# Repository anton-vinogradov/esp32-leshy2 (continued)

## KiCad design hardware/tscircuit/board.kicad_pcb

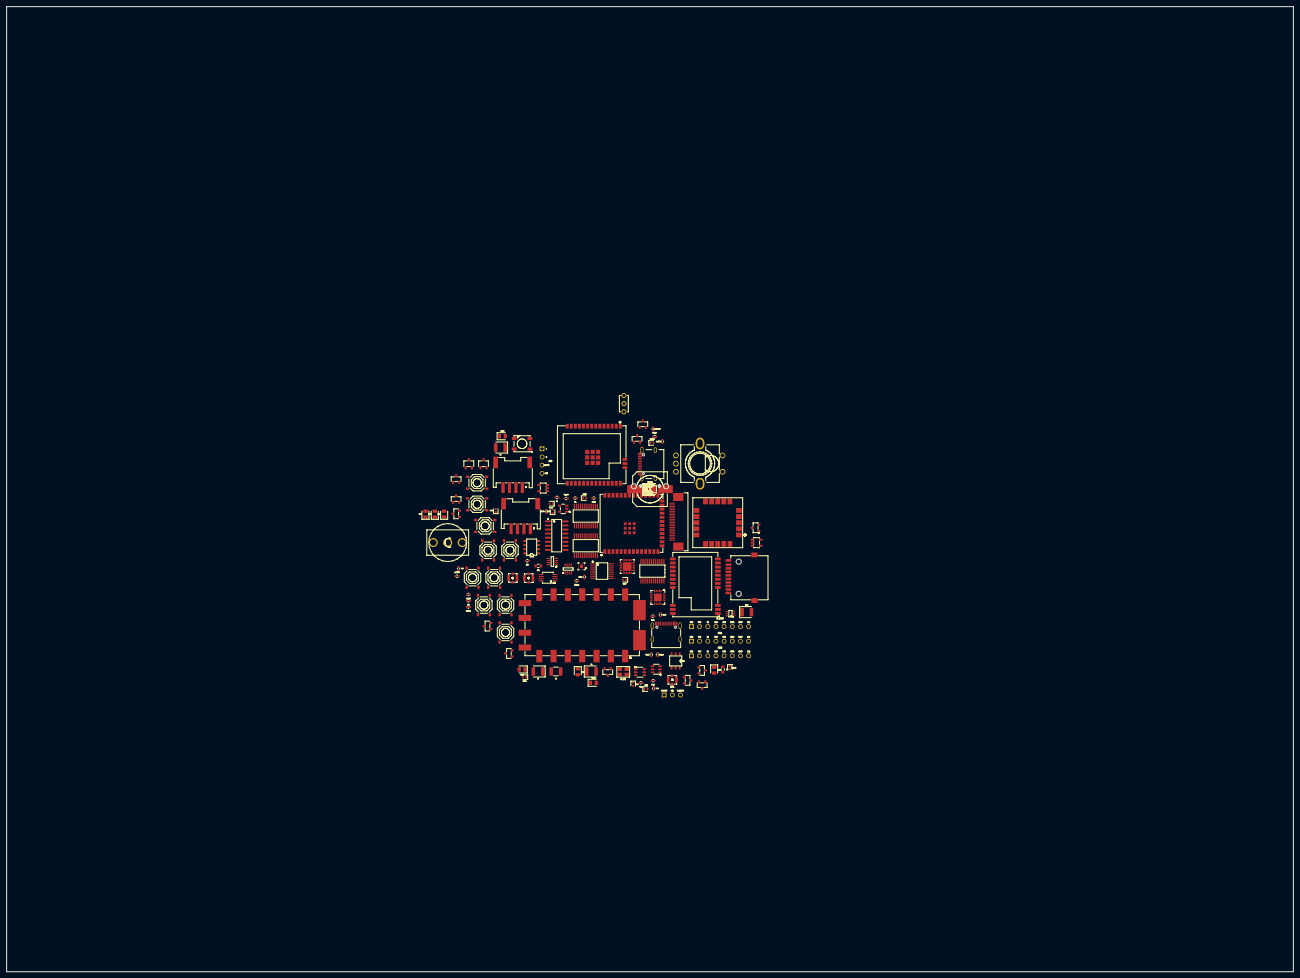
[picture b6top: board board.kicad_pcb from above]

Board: 2 copper layers, 400.0 x 300.0 mm, 191 parts (0 on the bottom side), 177 nets, no tracks yet.

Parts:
BL1: chip_soic6
BT1: chip_pinrow3
BT40: chip
CL1, CL2: 12pF; capacitor_cap0402
C_C5EN: 1uF; capacitor_cap0402
Cb20, Cb21, Cb22: 150uF; capacitor_cap1210
Cb23, Cb25: 100uF; capacitor_cap1210
Cbat: 10uF; capacitor_cap0805
Cbst4, Cbst5: 100nF; capacitor_cap0402
Cbtst: 47nF; capacitor_cap0402
Cbulk31: 330uF; capacitor_cap1210
Cbulk40: 10uF; capacitor_cap0805
Cbyp31: 100nF; capacitor_cap0402
Ccpl_si: 100pF; capacitor_cap0402
Cd20, Cd21, Cd22, Cd23, Cd25: 100nF; capacitor_cap0402
Cdc: 100nF; capacitor_cap0402
Cds1: 100nF; capacitor_cap0402
Cen: 1uF; capacitor_cap0402
Cin3, Cin5: 22uF; capacitor_cap0805
Cin3a: 1uF; capacitor_cap0402
Cinn: 0.1uF; capacitor_cap0402
Cinp: 0.1uF; capacitor_cap0402
Cio40: 100nF; capacitor_cap0402
Cir: 100nF; capacitor_cap0402
Cjk1, Cjk2: 220uF; capacitor_cap1210
Cmic: 1uF; capacitor_cap0402
Cout3, Cout5: 22uF; capacitor_cap0805
Cout3a: 2.2uF; capacitor_cap0402
Cpmid: 10uF; capacitor_cap0805
Cregn: 4.7uF; capacitor_cap0805
Csd1: 10uF; capacitor_cap0805
Csd2: 100nF; capacitor_cap0402
Csns: 47uF; capacitor_cap1210
Cu14, Cu51: 100nF; capacitor_cap0402
Cvbus: 10uF; capacitor_cap0805
Cvbusic: 1uF; capacitor_cap0402
Cvc: 0.1uF; capacitor_cap0402
Cvcc4, Cvcc5: 0.1uF; capacitor_cap0402
Cvcc32: 10uF; capacitor_cap0805
Cvcc40: 100nF; capacitor_cap0402
Cvdd: 0.1uF; capacitor_cap0402
Cvdd30: 1uF; capacitor_cap0402
Cvdd30b: 100nF; capacitor_cap0402
Cx1, Cx2: 10pF; capacitor_cap0402
D1: 1MΩ; resistor_res0603
D40, D41, D42: chip
D50, D51, D52, D53, D54, D55, D56, D57: LED; led_0603
DS1: chip
F1: 50mΩ; resistor_res1210
J1, J2, J40, J41, J50: chip
J30: chip_pinrow4
J_ANT_CC: chip
J_ANT_SI: chip
J_ANT_UHF: chip
J_LCD: chip
L1, L3: 2.2µH; inductor_1210
L2: 4.7µH; inductor_1210
LS1: 4Ω; resistor_res1210
LS2: 10mΩ; resistor_res1210
Lm315, Lm433, Lm868, Lm915: 1nH; inductor_0402
MK1: 2.2kΩ; resistor_res0603
Q1, Q2, Q50, Q51, Q52, Q53, Q54, Q55, Q56, Q57, Q58: chip
R1: 52.3kΩ; resistor_res0402
R2, R4: 10kΩ; resistor_res0402
R3: 31.6kΩ; resistor_res0402
R40, R41: 4.7kΩ; resistor_res0402
RT1: 10kΩ; resistor_res0603
RT2: 30.1kΩ; resistor_res0402
R_C5BOOT, R_C5EN, R_C5S27: 10kΩ; resistor_res0402
R_EN3H: 100kΩ; resistor_res0402
R_EN3L: 47kΩ; resistor_res0402
R_HC138EN: 10kΩ; resistor_res0402
R_RE3A, R_RE5: 100kΩ; resistor_res0402
Raam4, Raam5: 100kΩ; resistor_res0402
Rbst4, Rbst5: 20Ω; resistor_res0402
Rcbset: 10Ω; resistor_res0402
Rcc1, Rcc2: 5.1kΩ; resistor_res0402
Rd50, Rd51, Rd52, Rd53, Rd54, Rd55, Rd56: 4.7kΩ; resistor_res0402
Ren: 10kΩ; resistor_res0402
Rilim: 383Ω; resistor_res0402
Rin32: 10kΩ; resistor_res0402
Rir: 47Ω; resistor_res0603
Rmid: 300Ω; resistor_res0402
RsumL: 10kΩ; resistor_res0402
RsumR: 10kΩ; resistor_res0402
Rts_top: 5.23kΩ; resistor_res0402
Rvc: 470Ω; resistor_res0402
Rvdd: 470Ω; resistor_res0402
Rvm: 2kΩ; resistor_res0402
SW1, SW10: chip
SW11, SW12, SW13: 10mΩ; resistor_res1210
SW_BACK: chip
SW_DN: chip
SW_F1, SW_F2: chip
SW_LF: chip
SW_OK: chip
SW_OPT: chip
SW_RT: chip
SW_STOP: chip
SW_UP: chip
U2, U3, U4, U5, U6, U10, U11, U12, U13, U14, U23, U24, U25, U27, U28, U30, U31, U32, U33, U40, U50, U51: chip
U21, U22: chip_pinrow8_p2.54_doublerow
U44: chip_soic8
a_Rbias: 4.7kΩ; resistor_res0402
a_Y1: chip
m_U20: chip
rf_Rbias: 56kΩ; resistor_res0402
rf_U20: chip_pinrow8_p2.54_doublerow
rf_Y1: rf_Y1; crystal_crystal_3215_2

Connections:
.BT1 > .P_PLUS to .F1 > .pin1: BT1.1, F1.1
.Cbst4 > .pin1 to .U4 > .BST: Cbst4.1, U4.5
.Cbst4 > .pin2 to .Rbst4 > .pin1: Cbst4.2, Rbst4.1
.Cbst5 > .pin1 to .U5 > .BST: Cbst5.1, U5.5
.Cbst5 > .pin2 to .Rbst5 > .pin1: Cbst5.2, Rbst5.1
.Cbtst > .pin1 to .U2 > .BTST: Cbtst.1, U2.12
.Cinp > .pin2 to .U32 > .IN_POS: Cinp.2, U32.3
.Cjk1 > .pin2 to .J30 > .L: Cjk1.2, J30.1
.Cjk2 > .pin2 to .J30 > .R: Cjk2.2, J30.2
.Cmic > .pin2 to .U31 > .MIC_IN: Cmic.2, U31.18
.Cregn > .pin1 to .U2 > .REGN: Cregn.1, Rts_top.1, U2.11
.Cvcc4 > .pin1 to .U4 > .VCC: Cvcc4.1, U4.7
.Cvcc5 > .pin1 to .U5 > .VCC: Cvcc5.1, U5.7
.D50 > .pin1 to .Rd50 > .pin1: D50.1, Rd50.1
.D50 > .pin2 to .Q50 > .C: D50.2, Q50.3
.D51 > .pin1 to .Rd51 > .pin1: D51.1, Rd51.1
.D51 > .pin2 to .Q51 > .C: D51.2, Q51.3
.D52 > .pin1 to .Rd52 > .pin1: D52.1, Rd52.1
.D52 > .pin2 to .Q52 > .C: D52.2, Q52.3
.D53 > .pin1 to .Rd53 > .pin1: D53.1, Rd53.1
.D53 > .pin2 to .Q53 > .C: D53.2, Q53.3
.D54 > .pin1 to .Rd54 > .pin1: D54.1, Rd54.1
.D54 > .pin2 to .Q54 > .C: D54.2, Q54.3
.D55 > .pin1 to .Rd55 > .pin1: D55.1, Rd55.1
.D55 > .pin2 to .Q55 > .C: D55.2, Q55.3
.D56 > .pin1 to .Rd56 > .pin1: D56.1, Rd56.1
.D56 > .pin2 to .Q56 > .C: D56.2, Q56.3
.D57 > .pin1 to .Rir > .pin1: D57.1, Rir.1
.D57 > .pin2 to .Q58 > .C: D57.2, Q58.3
.F1 > .pin2 to .SW1 > .pin2: F1.2, SW1.2
.LS2 > .pin2 to .Q57 > .C: LS2.2, Q57.3
.R1 > .pin2 to .U4 > .FB: R1.2, R2.1, U4.8
.R3 > .pin2 to .U5 > .FB: R3.2, R4.1, U5.8
.R_EN3H > .pin2 to .U5 > .pin6: R_EN3H.2, R_EN3L.1, U5.6
.Raam4 > .pin1 to .U4 > .AAM: Raam4.1, U4.1
.Raam5 > .pin1 to .U5 > .AAM: Raam5.1, U5.1
.Rcbset > .pin1 to .U2 > .CBSET: Rcbset.1, U2.10
.Rcc1 > .pin1 to .J1 > .CC1: J1.13, Rcc1.1
.Rcc2 > .pin1 to .J1 > .CC2: J1.7, Rcc2.1
.Rilim > .pin1 to .U2 > .ILIM: Rilim.1, U2.8
.Rin32 > .pin2 to .Cinp > .pin1: Cinp.1, Rin32.2
.Rmid > .pin1 to .U2 > .MID: Rmid.1, U2.9
.Rvc > .pin1 to .U3 > .VC: Cvc.1, Rvc.1, U3.4
.Rvdd > .pin1 to .U3 > .VDD: Cvdd.1, Rvdd.1, U3.5
.Rvm > .pin1 to .U3 > .VM: Rvm.1, U3.3
.SW_BACK > .pin1 to .U14 > .IO0_5: SW_BACK.1, U14.9
.SW_DN > .pin1 to .U14 > .IO0_1: SW_DN.1, U14.5
.SW_F1 > .pin1 to .U14 > .IO1_0: SW_F1.1, U14.13
.SW_F2 > .pin1 to .U14 > .IO1_1: SW_F2.1, U14.14
.SW_LF > .pin1 to .U14 > .IO0_2: SW_LF.1, U14.6
.SW_OK > .pin1 to .U14 > .IO0_4: SW_OK.1, U14.8
.SW_OPT > .pin1 to .U14 > .IO0_6: SW_OPT.1, U14.10
.SW_RT > .pin1 to .U14 > .IO0_3: SW_RT.1, U14.7
.SW_STOP > .pin1 to .U14 > .IO0_7: SW_STOP.1, U14.11
.SW_UP > .pin1 to .U14 > .IO0_0: SW_UP.1, U14.4
.U3 > .CO to .Q2 > .G: Q2.1, U3.2
.U3 > .DO to .Q1 > .G: Q1.1, U3.1
.U4 > .SW to .L2 > .pin1: L2.1, Rbst4.2, U4.3
.U5 > .SW to .L3 > .pin1: L3.1, Rbst5.2, U5.3
.U23 > .DCOUPL to .Cdc > .pin1: Cdc.1, U23.5
.U23 > .RBIAS to .rf_Rbias > .pin1: U23.17, rf_Rbias.1
.U23 > .RF_N to .BL1 > .RFN: BL1.2, U23.13
.U23 > .RF_P to .BL1 > .RFP: BL1.1, U23.12
.U23 > .XOSC_Q1 to .rf_Y1 > .pin1: Cx1.1, U23.8, rf_Y1.1
.U23 > .XOSC_Q2 to .rf_Y1 > .pin2: Cx2.1, U23.10, rf_Y1.2
.U24 > .RF1 to .Lm315 > .pin1: Lm315.1, U24.3
.U24 > .RF2 to .Lm433 > .pin1: Lm433.1, U24.9
.U24 > .RF3 to .Lm868 > .pin1: Lm868.1, U24.2
.U24 > .RF4 to .Lm915 > .pin1: Lm915.1, U24.10
.U30 > .RCLK to .a_Y1 > .OSC1: CL1.1, CL2.1, U30.13, a_Y1.1
.U30 > .pin1 to .RsumR > .pin1: RsumR.1, U30.1
.U30 > .pin2 to .RsumL > .pin1: RsumL.1, U30.2
.U32 > .IN_NEG to .Cinn > .pin1: Cinn.1, U32.2
.U51 > .Y to .DS1 > .DIN: DS1.4, U51.4
.m_U20 > .IO27 to .R_C5S27 > .pin1: R_C5S27.1, m_U20.18
ANT_CC1101: J_ANT_CC.2, Lm315.2, Lm433.2, Lm868.2, Lm915.2
ANT_FM: Ccpl_si.1, J_ANT_SI.2, U30.6
ANT_HF_CB: Ccpl_si.2, U30.8
ANT_UHF: J_ANT_UHF.2, U31.12
BAT: Cbat.1, Cin3.1, Cin5.1, R_EN3H.1, Rvdd.2, SW1.1, U2.13, U2.14, U4.2, U5.2
BATM: BT1.2, Rcbset.2, Rmid.2, Rvc.2
BMINUS: BT1.3, Cvc.2, Cvdd.2, Q1.2, U3.6
BQ_CD: U2.3, U12.14
BQ_INT: U2.6, U12.13
BUZZER: Q57.1, U12.9
C5LINK_CS: U10.31, m_U20.10
C5LINK_DRDY: U10.32, m_U20.11
C5LINK_MISO: U10.30, m_U20.8
C5LINK_MOSI: U10.29, m_U20.23
C5LINK_SCK: U10.28, m_U20.21
C5_BOOT: R_C5BOOT.1, U13.10, m_U20.15, m_U20.27
C5_EN: C_C5EN.1, R_C5EN.1, U13.9, m_U20.3
C5_FLASH_RX: U10.36, m_U20.25
C5_FLASH_TX: U10.37, m_U20.24
CC1101_CS: U11.14, U23.7
CC1101_GDO0: U10.7, U23.6
CC1101_GDO2: U10.26, U23.3
CC1101_RF: BL1.3, U24.13
ENC_A: SW10.1, U10.33
ENC_B: SW10.3, U10.34
ENC_SW: SW10.5, U12.4
GND: BL1.4, BL1.5, BL1.6, BT40.2, CL1.2, CL2.2, C_C5EN.2, Cb20.2, Cb21.2, Cb22.2, Cb23.2, Cb25.2, Cbat.2, Cbulk31.2, Cbulk40.2, Cbyp31.2, Cd20.2, Cd21.2, Cd22.2, Cd23.2, Cd25.2, Cdc.2, Cds1.2, Cen.2, Cin3.2, Cin3a.2, Cin5.2, Cinn.2, Cio40.2, Cir.2, Cout3.2, Cout3a.2, Cout5.2, Cpmid.2, Cregn.2, Csd1.2, Csd2.2, Csns.2, Cu14.2, Cu51.2, Cvbus.2, Cvbusic.2, Cvcc4.2, Cvcc5.2, Cvcc32.2, Cvcc40.2, Cvdd30.2, Cvdd30b.2, Cx1.2, Cx2.2, D1.2, DS1.3, J1.1, J1.2, J1.3, J1.4, J1.5, J1.16, J2.1, J2.2, J2.3, J2.4, J2.5, J2.16, J30.3, J40.1, J40.5, J40.6, J41.1, J41.5, J41.6, J50.6, J50.10, J50.11, J50.12, J_ANT_CC.1, J_ANT_CC.3, J_ANT_CC.4, J_ANT_SI.1, J_ANT_SI.3, J_ANT_SI.4, J_ANT_UHF.1, J_ANT_UHF.3, J_ANT_UHF.4, J_LCD.1, J_LCD.2, J_LCD.13, J_LCD.17, J_LCD.23, J_LCD.24, J_LCD.25, J_LCD.26, MK1.2, Q2.2, Q50.2, Q51.2, Q52.2, Q53.2, Q54.2, Q55.2, Q56.2, Q57.2, Q58.2, R2.2, R4.2, RT1.2, RT2.2, R_EN3L.2, R_RE3A.2, R_RE5.2, Raam4.2, Raam5.2, Rcc1.2, Rcc2.2, Rilim.2, Rvm.2, SW10.2, SW10.4, SW10.6, SW10.7, SW11.2, SW12.2, SW13.2, SW_BACK.2, SW_DN.2, SW_F1.2, SW_F2.2, SW_LF.2, SW_OK.2, SW_OPT.2, SW_RT.2, SW_STOP.2, SW_UP.2, U2.19, U2.20, U2.24, U2.25, U4.4, U5.4, U6.2, U10.1, U10.40, U10.41, U10.42, U10.43, U10.44, U10.45, U10.46, U10.47, U10.48, U10.49, U11.5, U11.8, U12.2, U12.3, U12.12, U12.21, U13.2, U13.3, U13.12, U14.3, U14.12, U14.21, U21.1, U22.1, U23.16, U23.19, U23.21, U24.15, U25.1, U25.2, U25.3, U25.4, U25.5, U25.10, U25.11, U25.12, U25.20, U25.22, U27.3, U28.2, U30.7, U30.10, U30.15, U31.1, U31.9, U31.10, U31.19, U31.20, U32.7, U33.2, U40.1, U40.4, U40.5, U40.6, U40.10, U40.11, U40.15, U40.16, U40.20, U44.2, U50.2, U51.1, U51.3, a_Y1.2, m_U20.1, m_U20.28, m_U20.29, m_U20.30, m_U20.32, m_U20.33, m_U20.34, m_U20.35, m_U20.36, m_U20.37, m_U20.38, m_U20.39, m_U20.40, rf_Rbias.2, rf_U20.1
GPS_UART_RX: U10.11, U40.13
GPS_UART_TX: U10.24, U40.14
HC138_A: U10.12, U11.1
HC138_B: U10.17, U11.2
HC138_C: U10.18, U11.3
HC138_EN: R_HC138EN.1, U11.4, U12.19
I2C_SCL: D40.2, D41.2, J40.4, J41.4, R41.2, U2.5, U10.5, U12.22, U13.22, U14.22, U30.11, U44.4
I2C_SDA: D40.1, D41.1, J40.3, J41.3, R40.2, U2.4, U10.4, U12.23, U13.23, U14.23, U30.12, U44.3
IR_RX: U10.35, U50.1
IR_TX: Q58.1, U10.38
JACK_DET: J30.4, U13.7
LCD_BL_EN: J_LCD.12, U12.17
LCD_CS: J_LCD.5, U11.9
LCD_DC: J_LCD.6, U10.22
LCD_LEDA: J_LCD.20, J_LCD.21, J_LCD.22
LCD_LEDK: J_LCD.18, J_LCD.19
LCD_RESX: J_LCD.7, U12.10
LCD_TE: J_LCD.11, U10.23
LoRa_BUSY: U10.8, U25.14
LoRa_DIO1: U10.15, U25.13
LoRa_NRESET: U12.8, U25.15
LoRa_NSS: U11.10, U25.19
LoRa_RXEN: U25.6, U27.4
LoRa_TR: U12.15, U25.7, U27.2
MIC_HOT: Cmic.1, MK1.1, a_Rbias.2
MUX_OUT: Rin32.1, U33.4
MUX_SEL: U12.11, U33.6
PACKMID: Q1.3, Q2.3
PAM_SD: U12.16, U32.1
PCA9555_INT: U10.25, U12.1, U13.1, U14.1
PMID: Cpmid.1, L1.1, U2.21, U2.22
PTT_BTN: SW13.1, U13.4
RAIL_EN_3V3A: R_RE3A.1, U6.3, U13.6
RAIL_EN_5V: R_RE5.1, U4.6, U13.5
RFSW_A: U12.18, U24.7
RFSW_B: U13.8, U24.6
RFSW_C: U13.11, U24.5
S3_BOOT: SW12.1, U10.27
S3_EN: Cen.1, Ren.2, SW11.1, U10.3
SA868_PD: U12.6, U31.6
SA868_PTT: U12.5, U31.5
SA868_UART_RX: U10.10, U31.17
SA868_UART_TX: U10.9, U31.16
SA_AF: U31.3, U33.1
SD_CD: J50.9, U12.20
SD_CS: J50.2, U11.15
SI_AUDIO: RsumL.2, RsumR.2, U33.3
SNS: Csns.1, U2.15, U2.16
SPI_MISO: J50.7, J_LCD.10, U10.21, U21.7, U22.7, U23.2, U25.16, rf_U20.7
SPI_MOSI: J50.3, J_LCD.9, U10.19, U21.6, U22.6, U23.20, U25.17, rf_U20.6
SPI_SCK: J50.5, J_LCD.8, U10.20, U21.5, U22.5, U23.1, U25.18, rf_U20.5
SPK_M: Cjk2.1, LS1.2, U32.8
SPK_P: Cjk1.1, LS1.1, U32.5
SW: Cbtst.2, L1.2, U2.17, U2.18
Si4732_RST: U12.7, U30.9
TS: RT1.1, RT2.1, Rts_top.2, U2.7
USB_DM_C5: J2.10, J2.12, m_U20.13
USB_DM_S3: J1.10, J1.12, U10.13
USB_DP_C5: J2.9, J2.11, m_U20.14
USB_DP_S3: J1.9, J1.11, U10.14
V3V3: Cb20.1, Cb21.1, Cb22.1, Cb23.1, Cb25.1, Cbulk40.1, Cd20.1, Cd21.1, Cd22.1, Cd23.1, Cd25.1, Cio40.1, Cir.1, Cout3.1, Csd1.1, Csd2.1, Cu14.1, Cvcc40.1, D40.3, D41.3, D42.1, J40.2, J41.2, J50.4, J_LCD.3, J_LCD.4, L3.2, R3.1, R40.1, R41.1, R_C5BOOT.2, R_C5EN.2, R_C5S27.2, R_HC138EN.2, Rd50.2, Rd51.2, Rd52.2, Rd53.2, Rd54.2, Rd55.2, Rd56.2, Ren.1, U10.2, U11.6, U11.16, U12.24, U13.21, U13.24, U14.2, U14.24, U21.2, U22.2, U23.4, U23.9, U23.11, U23.14, U23.15, U23.18, U24.4, U25.9, U27.5, U28.5, U33.5, U40.2, U40.17, U44.1, U50.3, m_U20.2, rf_U20.2
V3V3A: Cout3a.1, Cvdd30.1, Cvdd30b.1, U6.5, U30.14, a_Rbias.1
V5: Cbulk31.1, Cbyp31.1, Cds1.1, Cin3a.1, Cout5.1, Cu51.1, Cvcc32.1, DS1.1, L2.2, LS2.1, R1.1, Rir.2, U6.1, U31.8, U32.6, U51.5
VBUS_C5: J2.6, J2.15
VBUS_S3: Cvbus.1, Cvbusic.1, D1.1, J1.6, J1.15, U2.23
V_BCKP: BT40.1, D42.3, U40.3
WS2812: U10.39, U51.2
nRF24_1_CSN: U11.13, rf_U20.4
nRF24_1_IRQ: U28.1, rf_U20.8
nRF24_2_CSN: U11.12, U21.4
nRF24_2_IRQ: U21.8, U28.3
nRF24_3_CSN: U11.11, U22.4
nRF24_3_IRQ: U22.8, U28.6
nRF24_CE: U10.6, U21.3, U22.3, rf_U20.3
nRF24_IRQ: U10.16, U28.4

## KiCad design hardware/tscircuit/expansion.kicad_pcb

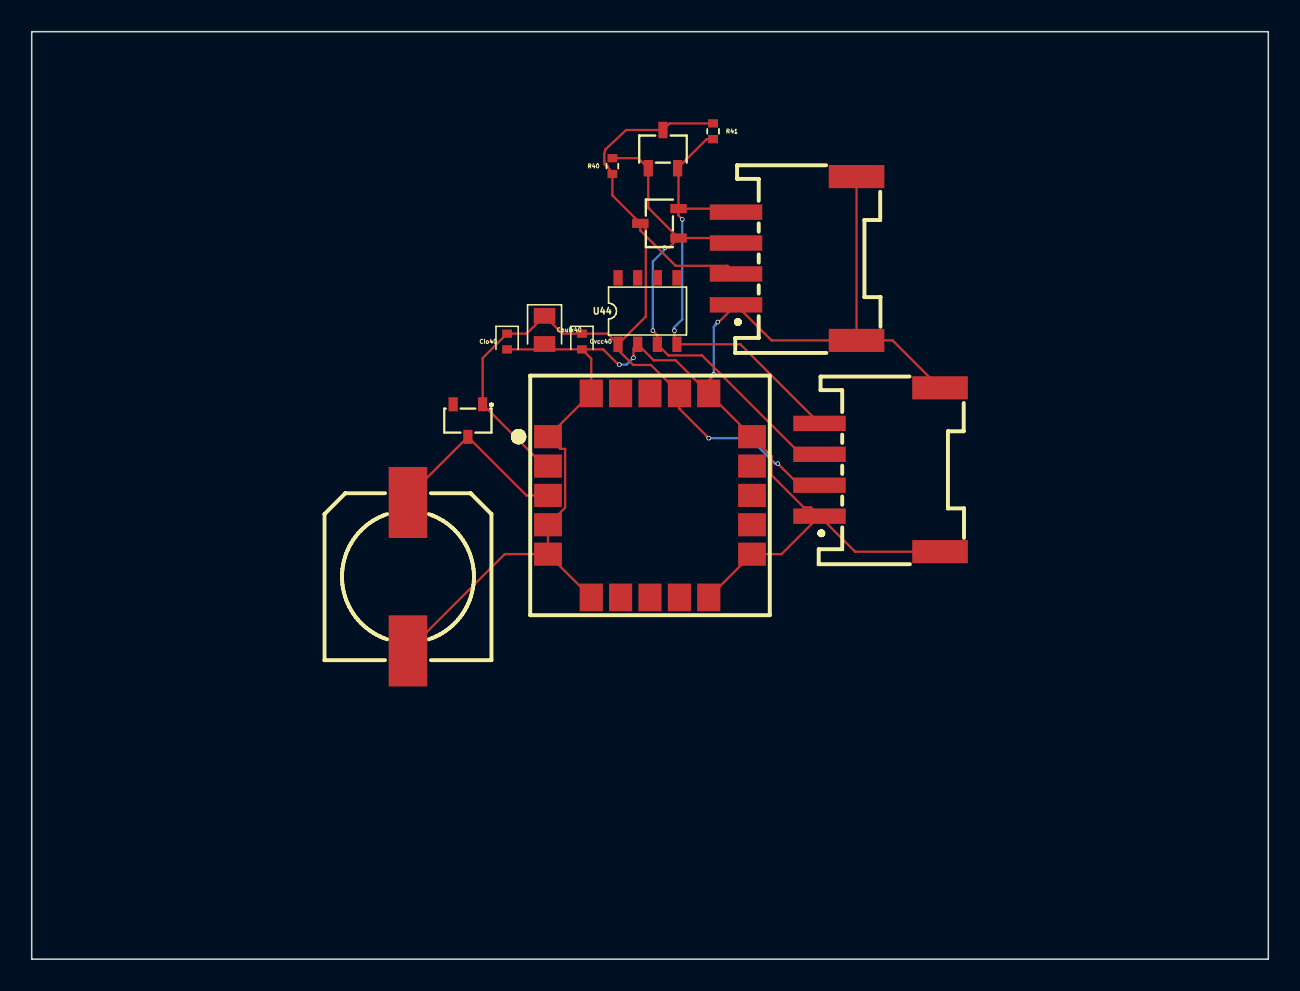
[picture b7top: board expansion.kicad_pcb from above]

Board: 2 copper layers, 80.0 x 60.0 mm, 13 parts (0 on the bottom side), 5 nets.

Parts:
BT40: chip
Cbulk40: 10uF; capacitor_cap0805
Cio40: 100nF; capacitor_cap0402
Cvcc40: 100nF; capacitor_cap0402
D40, D41, D42: chip
J40, J41: chip
R40, R41: 4.7kΩ; resistor_res0402
U40: chip
U44: chip_soic8

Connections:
GND: BT40.2, Cbulk40.2, Cio40.2, Cvcc40.2, J40.1, J40.5, J40.6, J41.1, J41.5, J41.6, U40.1, U40.4, U40.5, U40.6, U40.10, U40.11, U40.15, U40.16, U40.20, U44.2
I2C_SCL: D40.2, D41.2, J40.4, J41.4, R41.2, U44.4
I2C_SDA: D40.1, D41.1, J40.3, J41.3, R40.2, U44.3
V3V3: Cbulk40.1, Cio40.1, Cvcc40.1, D40.3, D41.3, D42.1, J40.2, J41.2, R40.1, R41.1, U40.2, U40.17, U44.1
V_BCKP: BT40.1, D42.3, U40.3

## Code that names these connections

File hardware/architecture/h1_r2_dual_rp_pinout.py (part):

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        errors.append("S3 dedicated ROM-UART routing must not retain the superseded isolator contract")
    for key, value in (
        ("mode", "dedicated_gpio"), ("uart0_gpio", {"tx": 43, "rx": 44}),
        ("hub_data_gpio", {"S3_HUB_D2": 7, "S3_HUB_D3": 8}),
    ):
        if routing.get(key) != value:
            errors.append(f"S3 dedicated ROM-UART routing metadata changed: {key}")
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        errors.append("RP2354B identity must join the registered SC1512-A4/A4 device")
    gpio_contacts = {name for name in rp.get("contacts", {}) if name.startswith("GPIO")}
    if gpio_contacts != {f"GPIO{gpio}" for gpio in range(48)}:
        errors.append("registered RP2354B package must expose GPIO0..47 exactly")

    for domain in ("hub_rp", "rf_rp"):
        block = source.get(domain, {})
        rows = block.get("pin_map", [])
        gpios = [row.get("gpio") for row in rows]
        if gpios != list(range(48)):
            errors.append(f"{domain}: pin_map must contain GPIO0..47 exactly once in order")
        if len({row.get("net") for row in rows}) != 48:
            errors.append(f"{domain}: net names must be unique")
        for row in rows:
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            errors.append(f"{domain}: reviewed H0 functional groups changed")
        h0_group_gpio_rows = [gpio for group in h0_groups for gpio in group]
        if len(h0_group_gpio_rows) != 48 or set(h0_group_gpio_rows) != set(range(48)):
            errors.append(f"{domain}: reviewed H0 functional groups must partition GPIO0..47 exactly once")
        if set(gpios) != set().union(*h0_groups):
            errors.append(f"{domain}: exact map does not cover the reviewed H0 groups")
        if budget.get("used") != h0[domain]["gpio_budget"]["used"]:
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        if (row.get("net"), row.get("direction"), row.get("controller")) != \
                (net, direction, "SPI1"):
            errors.append(f"rf_rp GPIO{gpio}: fixed SPI1 slave mux/direction changed")
    for gpio, net, direction in ((16, "VOICE_UART_TX", "out"), (17, "VOICE_UART_RX", "in")):
        row = rf_by_gpio[gpio]
        if (row.get("net"), row.get("direction"), row.get("controller")) != \
                (net, direction, "UART0"):
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
    c5_rows = {row["net"]: row for row in source["hub_rp"]["pin_map"] if row["net"].startswith("C5_SDIO_")}
    expected_c5_endpoints = {
        "C5_SDIO_CLK": (7, "C5 GPIO9 / module pad 11"),
        "C5_SDIO_CMD": (8, "C5 GPIO10 / module pad 12"),
        "C5_SDIO_D0": (9, "C5 GPIO8 / module pad 10"),
        "C5_SDIO_D1": (10, "C5 GPIO7 / module pad 9"),
        "C5_SDIO_D2": (11, "TS3USB221E 2D+", "C5 GPIO14 / module pad 14"),
        "C5_SDIO_D3": (12, "TS3USB221E 2D-", "C5 GPIO13 / module pad 13"),
    }
    if set(c5_rows) != set(expected_c5_endpoints):
        errors.append("Hub-side C5 bus must contain exactly CLK/CMD/DAT0..DAT3")
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        for row in c5_mux.get("c5_module", {}).get("signals", [])
    }
    if contract_map != {
        "SDIO_DAT1": ("GPIO7", 9), "SDIO_DAT0": ("GPIO8", 10),
        "SDIO_CLK": ("GPIO9", 11), "SDIO_CMD": ("GPIO10", 12),
        "SDIO_DAT3_USB_DM": ("GPIO13", 13), "SDIO_DAT2_USB_DP": ("GPIO14", 14),
    }:
        errors.append("joined C5 source no longer contains the exact fixed SDIO/module-pad map")
    route = c5_mux.get("production_mux_route", {})
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    if u219.get("accessories", {}).get("slot_population") != "exactly_one":
        errors.append("joined U219 source must require exactly-one U214/U219 population")
    pin10 = u219.get("pin_10_bidirectional_boundary", {})
    if pin10.get("host_gpio") != "RP GPIO12" or pin10.get("switch_mpn") != "SN74CBTLV1G125DCKR":
        errors.append("joined U219 source lost the exact GPIO12 bilateral boundary")
    if u219.get("pin_8_power_boundary", {}).get("host_gpio") != "RP GPIO14":
        errors.append("joined U219 source lost the exact GPIO14 reset/power boundary")
    shared_irq = u219.get("shared_irq_contract", {})
    if (shared_irq.get("connector_contact"), shared_irq.get("host_gpio"),
            shared_irq.get("host_net")) != (9, "RP GPIO13", "CAP_IRQ") \
            or "polarity is not published" not in shared_irq.get("u219_role", ""):
        errors.append("joined U219 source lost the profile-neutral GPIO13 IRQ contract")
    shared = u219.get("shared_spi_contract", {})
    if (shared.get("miso"), shared.get("clock"), shared.get("mosi")) != (
        "existing U214 MISO on RP GPIO44", "existing U214 SCK on RP GPIO45",
        "existing U214 MOSI on RP GPIO46",
    ):
        errors.append("joined U219 source changed the shared GPIO44..46 SPI assignment")
    shared_i2c = u219.get("shared_i2c_contract", {})
    if "RF RP GPIO30" not in shared_i2c.get("sda", "") \
            or "RF RP GPIO31" not in shared_i2c.get("scl", "") \
            or "TCA4307DGKR" not in (shared_i2c.get("sda", "") + shared_i2c.get("scl", "")):
        errors.append("joined U219 source changed the shared GPIO30/31 isolated I2C1 assignment")
    execution = " ".join(source.get("execution_gates", []))
    for token in ("TCA9803DGKR", "MAIN A-side", "AON B-side", "forbids external pull-ups"):
        if token not in execution:
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
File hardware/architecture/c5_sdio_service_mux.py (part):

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

EXPECTED_C5_SIGNALS = {
    "SDIO_DAT1": ("GPIO7", 9),
    "SDIO_DAT0": ("GPIO8", 10),
    "SDIO_CLK": ("GPIO9", 11),
    "SDIO_CMD": ("GPIO10", 12),
    "SDIO_DAT3_USB_DM": ("GPIO13", 13),
    "SDIO_DAT2_USB_DP": ("GPIO14", 14),
}
EXPECTED_MUX_PINS = {
    1: ("1D+", "C5_SERVICE_USB_DP_BRANCH"),
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           "SDIO pull-ups must be fitted on CMD and DAT0..DAT3 only")
    clock_bias = conditioning.get("sdio_clock_bias", {})
    _error(errors, clock_bias.get("signal") == "CLK"
           and clock_bias.get("gpio") == "GPIO9"
           and clock_bias.get("fitted_pull") is None
           and "not populated" in clock_bias.get("dnp_footprint", ""),
           "SDIO CLK must have no fitted pull and retain only a DNP bias footprint")
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           "USB D+/D- require branch-local 22/33-ohm port1 series footprints")

    straps = {row.get("gpio"): row for row in contract.get("edge_straps", {}).get("contacts", [])}
    _error(errors, straps.get("GPIO25", {}).get("module_pad") == 26
           and straps.get("GPIO25", {}).get("latched_value") == 1,
           "GPIO25 must be module pad 26 and strap high for rising-edge sample")
    _error(errors, straps.get("GPIO3", {}).get("module_pad") == 5
           and straps.get("GPIO3", {}).get("latched_value") == 0,
           "GPIO3/MTDI must be module pad 5 and strap low for falling-edge drive")
    _error(errors, contract.get("edge_straps", {}).get("hold_after_c5_en_release_ms_min", 0) >= 3,
           "C5 strap levels must remain valid for at least 3 ms after EN release")
    boot = contract.get("boot_straps", {})
    _error(errors, boot.get("contacts") == [
        {"gpio": "GPIO27", "module_pad": 18, "net": "C5_GPIO27_FIXED_HIGH", "pullup_ohm": 10000},
        {"gpio": "GPIO28", "module_pad": 15, "net": "C5_BOOT_N", "pullup_ohm": 10000, "button_series_ohm": 1000},
    ] and boot.get("joint_download_boot_0") == {"GPIO27": 1, "GPIO28": 0}
           and boot.get("application_boot") == {"GPIO27": 1, "GPIO28": 1}
           and type(boot.get("hold_after_en_release_ms_min")) is int
           and boot["hold_after_en_release_ms_min"] == 3
           and boot.get("sampled_levels_and_timing_qualified") is False
           and c5.get("contacts", {}).get("GPIO27", {}).get("physical") == "18"
           and c5.get("contacts", {}).get("GPIO28", {}).get("physical") == "15",
           "C5 BOOT GPIO27/28 topology, 3-ms hold or unqualified boundary changed")

    ownership = contract.get("ownership", {})
    latch = ownership.get("latch", {})
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
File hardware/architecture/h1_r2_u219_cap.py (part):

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        errors.append("U219 official 14-contact table changed or is incomplete")

    pin8 = model.get("pin_8_power_boundary", {})
    if pin8.get("connector_contact") != 8 or pin8.get("host_gpio") != "RP GPIO14":
        errors.append("contact 8 must reuse RP GPIO14")
    if pin8.get("fail_safe_default") != "low":
        errors.append("U219 POWER_EN must fail low")
    power = model.get("protected_5v_boundary", {})
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        errors.append("official U219 contact-7 conflict must block power until received-unit proof")

    pin10 = model.get("pin_10_bidirectional_boundary", {})
    if pin10.get("connector_contact") != 10 or pin10.get("host_gpio") != "RP GPIO12":
        errors.append("contact 10 must reuse RP GPIO12 bidirectionally")
    if pin10.get("switch_mpn") != "SN74CBTLV1G125DCKR":
        errors.append("contact 10 requires the audited bilateral switch")
    aon = pin10.get("aon_enable", {})
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        errors.append("contact 10 /OE requires the audited AON open-drain inverter")
    if aon.get("command_source") != "existing U214_READY; the signed profile is admitted before any upstream branch request can make READY high":
        errors.append("pin 10 /OE must derive from the existing qualified READY plane without a GPIO")
    if aon.get("supply") != "AON_SAFE_3V3" or "disconnects pin 10" not in aon.get("loss_behavior", ""):
        errors.append("pin 10 must disconnect on qualification loss from the AON plane")
    for token in ("u214_return_buffer channel 1", "u214_series_busy"):
        if not any(token in row for row in pin10.get("supersedes", [])):
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    required_base_routes = {
        ("u214_host_buffer_a.1Y", "u214_series_rst.END_1", "U214_RST_BUFFERED"),
        ("u214_series_rst.END_2", "u214_esd_a.D2_PLUS", "U214_RST_CONNECTOR"),
        ("u214_esd_a.D2_PLUS", "u214_connector.PIN_8", "U214_RST_CONNECTOR"),
        ("u214_connector.PIN_10", "u214_esd_b.D2_MINUS", "U214_BUSY_CONNECTOR"),
        ("evidence_mask.P17", "evidence_mask_p17_pulldown.END_1", "EVIDENCE_MASK_UNUSED_P17"),
        ("evidence_or_4.K2", "abstract:no-connect", "EVIDENCE_OR_4_UNUSED_DIODE_NC"),
        ("evidence_or_4.A_COMMON", "safety_controller.PA22", "ANY_TX_AON_N"),
    }
    missing = sorted(required_base_routes - routes)
    if missing:
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    i2c = model.get("shared_i2c_contract", {})
    if i2c.get("owner") != "rear RF RP2354B I2C1 domain":
        errors.append("U219 I2C must reuse the rear RF RP I2C1 domain")
    if "contact 3 SCL" not in i2c.get("scl", "") or "RF RP GPIO31" not in i2c.get("scl", ""):
        errors.append("U219 contact 3 must reuse the isolated I2C1 SCL path to RF GPIO31")
    if "contact 4 SDA" not in i2c.get("sda", "") or "RF RP GPIO30" not in i2c.get("sda", ""):
        errors.append("U219 contact 4 must reuse the isolated I2C1 SDA path to RF GPIO30")
    if "TCA4307DGKR" not in i2c.get("scl", "") or "TCA4307DGKR" not in i2c.get("sda", ""):
        errors.append("U219 SCL/SDA must retain the existing hot-plug/stuck-low isolator")
    if "no new GPIO" not in i2c.get("isolation", ""):
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
    irq = model.get("shared_irq_contract", {})
    if (irq.get("connector_contact"), irq.get("host_gpio"), irq.get("host_net")) != \
            (9, "RP GPIO13", "CAP_IRQ"):
        errors.append("U214/U219 contact 9 must use the profile-neutral CAP_IRQ path on RP GPIO13")
    if "active-high" not in irq.get("u214_role", ""):
        errors.append("U214 DIO1 active-high semantics must remain profile metadata")
    if "polarity is not published" not in irq.get("u219_role", ""):
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
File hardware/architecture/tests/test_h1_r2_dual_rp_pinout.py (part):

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            self.source, broken_h0, MODULE.load(MODULE.C5_MUX), MODULE.load(MODULE.U219)
        )
        self.assertIn(
            "rf_rp: reviewed H0 functional groups must partition GPIO0..47 exactly once",
            errors,
        )

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        self.assertNotIn("s3_rom_uart_isolation", self.source)
        routing = self.source["s3_rom_uart_routing"]
        self.assertEqual({"tx": 43, "rx": 44}, routing["uart0_gpio"])
        self.assertEqual({"S3_HUB_D2": 7, "S3_HUB_D3": 8}, routing["hub_data_gpio"])
        self.assertTrue(all(value is False for value in routing["qualification"].values()))
        s3 = {row["gpio"]: row for row in self.h0["s3"]["pin_map"]}
        for gpio, expected in {
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        }.items():
            self.assertEqual(expected, tuple(s3[gpio][key] for key in ("net", "peripheral", "direction")))
        hub = {row["gpio"]: row for row in self.source["hub_rp"]["pin_map"]}
        self.assertEqual("S3 GPIO7 through GPIO matrix", hub[2]["endpoint"])
        self.assertEqual("S3 GPIO8 through GPIO matrix", hub[3]["endpoint"])
        candidate = MODULE.load(MODULE.G2F)
        for russian in (False, True):
            page = MODULE.render_public(self.source, candidate, russian)
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
    def test_s3_rom_uart_rejects_mismatched_hub_pair_or_lost_startup_guards(self):
        for gpio in (2, 3):
            for key, value in (("net", "S3_HUB_D3" if gpio == 2 else "S3_HUB_D2"),
                               ("endpoint", "S3 GPIO43 through ROM-UART isolation"),
                               ("controller", "GPIO"), ("direction", "out"),
                               ("reset", "input/high-Z")):
                with self.subTest(gpio=gpio, key=key):
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                del broken["s3_rom_uart_routing"][key]
                self.assertTrue(MODULE.validate_s3_rom_uart_routing(broken, self.h0))
        for key, wrong in (("mode", "shared_gpio"), ("uart0_gpio", {"tx": 7, "rx": 8}),
                           ("hub_data_gpio", {"S3_HUB_D2": 43, "S3_HUB_D3": 44}),
                           ("uart0_shared_with_hub", True), ("requires_rom_uart_isolator", True),
                           ("uart0_shared_with_hub", 0)):
            with self.subTest(key=key, wrong=wrong):
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        self.assertEqual([], audit["authority"]["remaining_h2_gates"])
        c5 = [row for row in self.source["hub_rp"]["pin_map"] if row["net"].startswith("C5_SDIO_")]
        self.assertEqual(6, len(c5))
        self.assertIn("C5 GPIO9 / module pad 11", c5[0]["endpoint"])
        self.assertIn("TS3USB221E 2D+", c5[4]["endpoint"])
        self.assertIn("TS3USB221E 2D-", c5[5]["endpoint"])
        hub = {row["gpio"]: row for row in self.source["hub_rp"]["pin_map"]}
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        errors = MODULE.validate(
            broken, self.h0, MODULE.load(MODULE.C5_MUX), MODULE.load(MODULE.U219)
        )
        self.assertIn("HUB_RF_SCK: endpoint net does not match both RP pin maps", errors)
        self.assertIn("hub_rp: DMA used count does not match allocations", errors)

    def test_real_rp_identity_fixed_mux_and_pio_windows_fail_closed(self):
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        unsafe_reset = copy.deepcopy(self.source)
        unsafe_reset["hub_rp"]["pin_map"][36]["reset"] = "unsafe-but-nonempty"
        self.assertIn(
            "hub_rp GPIO36: reset state is not fail-closed/high-Z",
            MODULE.validate(unsafe_reset, self.h0, c5, u219),
        )

        no_audio_isolation = copy.deepcopy(self.source)
        no_audio_isolation["rf_rp"]["pin_map"][0]["endpoint"] = "direct ES8311 BCLK"
        self.assertTrue(any(
            "rf_rp GPIO0: audio path lacks reset-off" in error
            for error in MODULE.validate(no_audio_isolation, self.h0, c5, u219)
        ))

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        self.assertEqual(MODULE.render_public(self.source, candidate, True), MODULE.DOC_RU.read_text(encoding="utf-8"))
        self.assertIn("TS3USB221ERSER/C129313", MODULE.DOC_EN.read_text(encoding="utf-8"))
        self.assertIn("TCA9803DGKR/C2687966", MODULE.DOC_EN.read_text(encoding="utf-8"))
        self.assertIn("S3 GPIO7 through GPIO matrix", MODULE.DOC_EN.read_text(encoding="utf-8"))
        self.assertIn("Dedicated S3 ROM-UART routing", MODULE.DOC_EN.read_text(encoding="utf-8"))


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
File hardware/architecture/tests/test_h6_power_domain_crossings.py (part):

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
    def test_current_scan_finds_both_c5_inputs_without_claiming_damage(self):
        result = self.run_gate()
        for endpoint, net in (("c5.GPIO23", "EV_N1_C5"), ("c5.GPIO24", "EV_N7_IR")):
            row = self.crossing(result, endpoint)
            self.assertEqual(net, row["net"])
            self.assertEqual("missing_off_state_tolerance", row["finding_kind"])
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        for row in self.data["nets"]["rows"]:
            if row["net"] == "EV_N1_C5":
                row["net"] = "RENAMED_ANY_SIGNAL"
        self.assertEqual("RENAMED_ANY_SIGNAL", self.crossing(self.run_gate(), "c5.GPIO23")["net"])

    def test_missing_receiver_contact_cannot_silently_reduce_coverage(self):
        self.data["nets"]["rows"].remove(self.endpoint("c5.GPIO23"))
        with self.assertRaisesRegex(ValueError, "contact coverage"):
            self.run_gate()

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        rows = [r for r in self.data["nets"]["rows"] if r["instance"] == "c5"]
        self.data["nets"]["rows"].extend({**r, "instance": new["instance"], "reference": new["reference"],
                                         "endpoint": new["instance"] + "." + r["contact"]} for r in rows)
        self.assertEqual("EV_N1_C5", self.crossing(self.run_gate(), "extra_main_receiver.GPIO23")["net"])

    def test_open_drain_without_live_pullup_is_not_high_source(self):
        # Move only the actual comparator and receiver to an otherwise empty
        # local net. No LED/resistor/TCA GPIO is silently followed into it.
        self.endpoint("evidence_cmp_a.OUT2")["net"] = "OD_ONLY"
        self.endpoint("c5.GPIO23")["net"] = "OD_ONLY"
        self.assertFalse(any(r["net"] == "OD_ONLY" for r in self.run_gate()["crossings"]))

    def test_live_pullup_is_detected_even_with_only_open_drain_driver(self):
        for endpoint in ("evidence_cmp_a.OUT2", "c5.GPIO23", "c5_evidence_output_pullup.END_2"):
            self.endpoint(endpoint)["net"] = "OD_PLUS_RESISTOR"
        row = self.crossing(self.run_gate(), "c5.GPIO23")
        self.assertEqual(["resistor_to_live_rail"], [r["kind"] for r in row["sources"]])

    def test_main_pullup_does_not_become_aon_source(self):
        for endpoint in ("evidence_cmp_a.OUT2", "c5.GPIO23", "c5_evidence_output_pullup.END_2"):
            self.endpoint(endpoint)["net"] = "OD_PLUS_MAIN_RESISTOR"
        self.endpoint("c5_evidence_output_pullup.END_1")["net"] = "3V3_MAIN"
        self.assertFalse(any(r["net"] == "OD_PLUS_MAIN_RESISTOR" for r in self.run_gate()["crossings"]))
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        self.assertEqual("potential_direct_high_drive", row["sources"][0]["kind"])

    def test_input_tied_directly_to_assumed_live_rail_is_discovered(self):
        self.endpoint("c5.GPIO23")["net"] = "AON_SAFE_3V3"
        row = self.crossing(self.run_gate(), "c5.GPIO23")
        source = next(r for r in row["sources"] if r["kind"] == "assumed_live_rail")
        self.assertEqual("AON_SAFE_3V3", source["net"])
        self.assertFalse(source["physical_voltage_proven"])
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
    def test_same_net_name_on_unconnected_boards_is_not_a_connection(self):
        self.endpoint("safe_latch.Q_N")["net"] = "TWO_LOCAL_LABELS"
        self.endpoint("c5.GPIO23")["net"] = "TWO_LOCAL_LABELS"
        self.assertFalse(any(r["net"] == "TWO_LOCAL_LABELS" for r in self.run_gate()["crossings"]))

    def test_m1_mismatch_cannot_join_unrelated_nets(self):
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
    def test_generic_output_ioff_prose_never_clears_input_review(self):
        self.data["devices"]["devices"]["esp32_c5_wroom_1u_n8r8"]["electrical_contract"] = {"partial_power_down": "Ioff supports outputs at VCC=0"}
        self.assertEqual("missing_off_state_tolerance", self.crossing(self.run_gate(), "c5.GPIO23")["finding_kind"])

    def test_exact_input_evidence_is_not_an_unmodeled_voltage_proof(self):
        proof = self.proof()
        result = self.run_gate(proofs=[proof], proof_hashes={proof["source"]["path"]: proof["source"]["sha256"]})
        row = self.crossing(result, "c5.GPIO23")
        self.assertEqual("off_state_input_evidence_requires_voltage_review", row["finding_kind"])
        self.assertFalse(row["qualified"])
        self.assertFalse(row["pin_voltage_bounded"])
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                self.run_gate(proofs=[{**proof, "input_v": value}], proof_hashes=hashes)

    def test_native_and_material_duplicates_fail_closed(self):
        mutations = [lambda: self.data["nets"]["rows"].append(copy.deepcopy(self.endpoint("c5.GPIO23"))),
                     lambda: self.data["instances"]["rows"].append(copy.deepcopy(self.data["instances"]["rows"][0])),
                     lambda: self.data["material"]["groups"][0]["contacts"].append(copy.deepcopy(self.data["material"]["groups"][0]["contacts"][0]))]
        for mutate in mutations:
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
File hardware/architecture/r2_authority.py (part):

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    for domain, instance in instance_by_domain.items():
        rows = [dict(row) for row in allocations if row.get("instance") == instance]
        for row in rows:
            if row.get("contact") == "PA0":
                row.update(
                    net="HUB_SAFE_I2C_SDA",
                    peers=["hub_rp.GPIO42", "M1.32"],
                    endpoint="Hub RP I2C1 through TCA9803DGKR SDAA/SDAB powered-off boundary and M1.32",
                )
            elif row.get("contact") == "PA11":
                row.update(
                    net="HUB_SAFE_I2C_SCL",
                    peers=["hub_rp.GPIO43", "M1.33"],
                    endpoint="Hub RP I2C1 through TCA9803DGKR SCLA/SCLB powered-off boundary and M1.33",
                )
        result[domain] = rows
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    if pin_authority.get("marker") != "H1-R2.31":
        errors.append("current dual-RP pin authority must carry marker H1-R2.31")
    if any([row.get("gpio") for row in rows] != list(range(48)) for rows in exact_pin_maps.values()):
        errors.append("current dual-RP pin authority must map GPIO0..47 exactly once per RP")
    if len(pin_authority.get("m1_binding", [])) != 5:
        errors.append("current dual-RP pin authority must bind exactly five Hub-RF M1 signals")
    pre_h2_gates = pin_authority.get("authority_chain", {}).get("remaining_h2_gates", [])
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
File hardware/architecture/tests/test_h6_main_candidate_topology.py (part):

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                        self.assertEqual(row['pads'], [physical])
                        self.assertEqual(row['disposition'], 'no_connect' if net is None else 'connected')
                self.assertEqual(self.pin('exp_main_monitor_bypass', '1', candidate)['net'], supply)
                self.assertEqual(self.pin('exp_main_monitor_bypass', '2', candidate)['net'], 'POWER_GROUND')
                self.assertEqual(F(self.instance('exp_main_monitor_bypass', candidate)
                                   ['generic_candidate']['value_f_exact']), F('0.0000001'))

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            self.assertEqual(self.pin(name, pad)['net'], net)
        self.assertEqual(self.instance('main_efuse_pg_top')['reference'], 'R66')
        self.assertEqual(self.instance('main_efuse_pg_bottom')['reference'], 'R65')
        self.assertFalse(any(r['net'] == 'MAIN_EFUSE_PGTH' for r in self.candidate['pins']))
        self.assertFalse(any(r['endpoint'] == 'main_efuse.PGTH' for r in self.candidate['pins']))

    def test_five_values_are_generic_and_both_selected_divider_classes_are_used(self):
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            elif mutation == 'component':
                self.instance('power_fault_pullup')['mpn'] = 'substituted part'
            else:
                self.pin('power_fault_pullup', '1')['net'] = 'AON_SAFE_3V3'
            with self.subTest(mutation=mutation), self.assertRaises(ValueError):
                self.validate()

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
